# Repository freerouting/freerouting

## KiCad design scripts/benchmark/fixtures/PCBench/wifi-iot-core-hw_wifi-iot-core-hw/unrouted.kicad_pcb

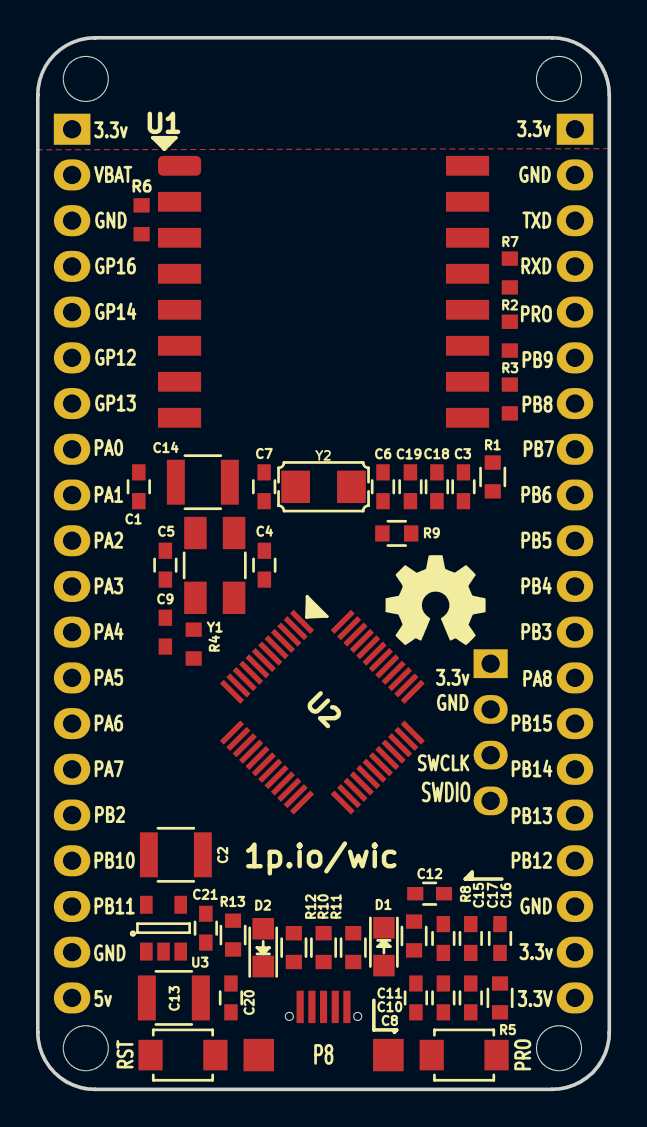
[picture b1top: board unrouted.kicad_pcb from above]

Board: 2 copper layers, 31.8 x 58.4 mm, 52 parts (0 on the bottom side), 54 nets, no tracks yet.

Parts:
C1, C9, C10, C11, C12, C15, C17, C19, C20: 0.1uF; C_0603
C2, C13, C14: 10uF-50v; C_1210
C3: 100nF; C_0603
C4, C5: 10pF; C_0603
C6: 15pF; C_0603
C7: 15pf; C_0603
C8: 470pF; C_0603
C16, C18: 1uF; C_0603
C21: 10nF; C_0603
D1: Led GPIO16; LED_0805
D2: Led; LED_0805
P1, P2: CONN_01X20; Pin_Header_Straight_1x20
P3, P4, P5, P6: CONN_01X01; MountingHole_2.5mm
P7: CONN_01X04; Pin_Header_Straight_1x04
P8: USB; Micro_usb_B_smd
PRO: SW_PUSH_SMALL_H; SW_SPST_B3U-1000P-B
R1, R6, R7, R8, R13: 10k; R_0603
R2, R3, R4, R5: 10K; R_0603
R9: 0R; R_0603
R10: 1.5K; R_0603
R11, R12: 22; R_0603
RST: RST; SW_SPST_B3U-1000P-B
U1: ESP-07v2; ESP-07v2-smd-16pin
U2: STM32F103C8Tx; LQFP-48_Pin1.7x0.3mm_Pitch0.5mm
U3: LP2985LV; SOT-23-5
VAL**: oshw_logo_500; logo5
Y1: 8MHz; Crystal_SMD_5032_4Pads
Y2: 32.687; crystal_smd_32.768_2Pin

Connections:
+3V3: C1.1, C2.1, C10.2, C11.2, C12.1, C14.1, C15.2, C16.2, C17.2, P1.1, P2.1, P2.19, P2.20, P7.1, R2.1, R4.2, R5.2, R6.1, R7.1, R8.1, R9.2, R13.1, U1.8, U2.9, U2.24, U2.36, U2.48, U3.5
+5V: C13.1, C20.1, P1.20, P8.1, U3.1, U3.3
/CH_PD: R6.2, U1.3, U2.19
/ESP_PRO: C8.1, P2.5, PRO.1, R5.1, R7.2, U1.12, U2.38
/ESP_RST: U1.1, U2.18
/ESP_RXD: P2.4, U1.15, U2.30
/ESP_TXD: P2.3, U1.16, U2.31
/GPIO16: D1.1, P1.4, U1.4
/RST: C9.1, R4.1, RST.1, U2.7
/SWCLK: P7.3, U2.37
/SWDIO: P7.4, U2.34
/USB_DIS: R10.1, U2.2
/USB_DM: R12.1, U2.32
/USB_DP: R11.1, U2.33
/VBAT: C3.2, C18.2, C19.2, P1.2, R9.1, U2.1
GNDREF: C1.2, C2.2, C3.1, C4.2, C5.2, C6.2, C7.2, C8.2, C9.2, C10.1, C11.1, C12.2, C13.2, C14.2, C15.1, C16.1, C17.1, C18.1, C19.1, C20.2, C21.2, D2.1, P1.3, P1.19, P2.2, P2.18, P8.4, P8.5, PRO.2, R1.2, R3.2, RST.2, U1.9, U3.2
GPIO12: P1.6, U1.6
GPIO13: P1.7, U1.7
GPIO14: P1.5, U1.5
unnamed: C4.1, U2.5, Y1.1
unnamed: C5.1, U2.6, Y1.2
unnamed: C6.1, U2.3, Y2.1
unnamed: C7.1, U2.4, Y2.2
unnamed: C21.1, U3.4
unnamed: D1.2, R8.2
unnamed: D2.2, R13.2
unnamed: P8.2, R12.2
unnamed: P8.3, R10.2, R11.2
unnamed: R1.1, U2.44
unnamed: R2.2, U1.11
unnamed: R3.1, U1.10
PA0: P1.8, U2.10
PA1: P1.9, U2.11
PA2: P1.10, U2.12
PA3: P1.11, U2.13
PA4: P1.12, U2.14
PA5: P1.13, U2.15
PA6: P1.14, U2.16
PA7: P1.15, U2.17
PA8: P2.13, U2.29
PB2: P1.16, U2.20
PB3: P2.12, U2.39
PB4: P2.11, U2.40
PB5: P2.10, U2.41
PB6: P2.9, U2.42
PB7: P2.8, U2.43
PB8: P2.7, U2.45
PB9: P2.6, U2.46
PB10: P1.17, U2.21
PB11: P1.18, U2.22
PB12: P2.17, U2.25
PB13: P2.16, U2.26
PB14: P2.15, U2.27
PB15: P2.14, U2.28

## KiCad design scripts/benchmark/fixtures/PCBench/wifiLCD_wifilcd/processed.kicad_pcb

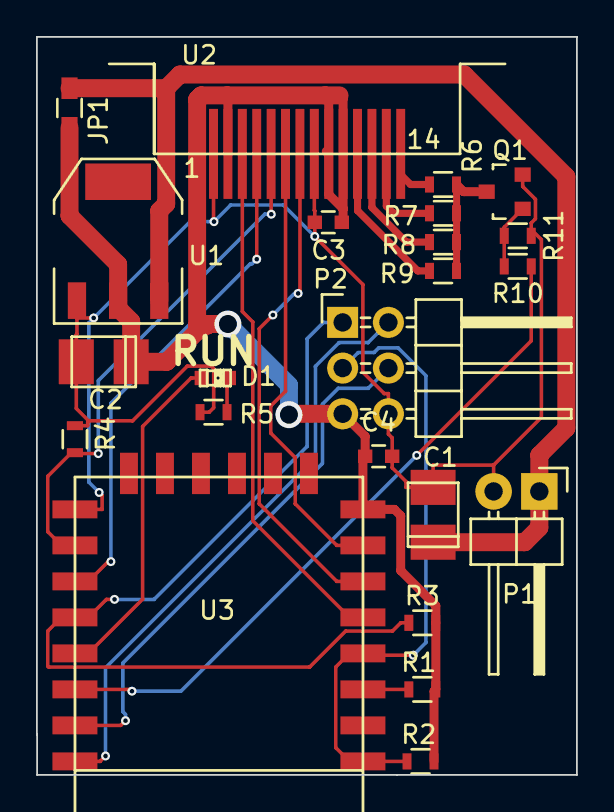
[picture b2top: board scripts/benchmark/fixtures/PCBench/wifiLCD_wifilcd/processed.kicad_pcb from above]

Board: 2 copper layers, 30.0 x 41.0 mm, 23 parts (0 on the bottom side), 22 nets.

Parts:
C1: 22uF 25V; TantalC_SizeT_EIA-3528
C2: 100uF 6.3v; TantalC_SizeT_EIA-3528
C3, C4: 100n; C_0603
D1: LED; LED-0603
JP1: JUMPER; R_0603_HandSoldering
P1: CONN_01X02; Pin_Header_Angled_1x02
P2: CONN_01X06; Pin_Header_Angled_2x03
Q1: BSS138; SOT-23
R1, R2, R3, R4: 10K; R_0603
R5: 220; R_0603
R6, R7, R8, R9: 4R7; R_0603
R10: 100k; R_0603
R11: 10; R_0603
U1: AP1117D33; SOT-223
U2: TM022HDH26; TM022HDH26_PADSONLY
U3: ESP-12E

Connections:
+3V3: C2.1, C3.1, C4.1, JP1.2, P2.5, R1.1, R2.1, R3.1, U1.2, U2.2, U2.9, U2.10, U3.8
+5V: C1.1, JP1.1, P1.1, U1.3
/BL: R11.2, U3.20
/CS: R4.1, U2.5, U3.16
/DC: U2.4, U3.17
/DTR: P2.1, R3.2, U3.18
/MISO: U2.7, U3.6
/MOSI: U2.6, U3.7
/RTS: P2.3, R2.2, U3.1, U3.4
/RX: P2.2, U3.22
/SCL: U2.3, U3.5
/TX: P2.4, U3.21
GND: C1.2, C2.2, C3.2, C4.2, P1.2, P2.6, Q1.2, R4.2, R5.2, R10.1, U1.1, U2.1, U2.8, U3.15
unnamed: D1.1, R5.1
unnamed: D1.2, U3.19
unnamed: Q1.1, R10.2, R11.1
unnamed: Q1.3, R6.1, R7.1, R8.1, R9.1
unnamed: R1.2, U3.3
unnamed: R6.2, U2.14
unnamed: R7.2, U2.13
unnamed: R8.2, U2.12
unnamed: R9.2, U2.11

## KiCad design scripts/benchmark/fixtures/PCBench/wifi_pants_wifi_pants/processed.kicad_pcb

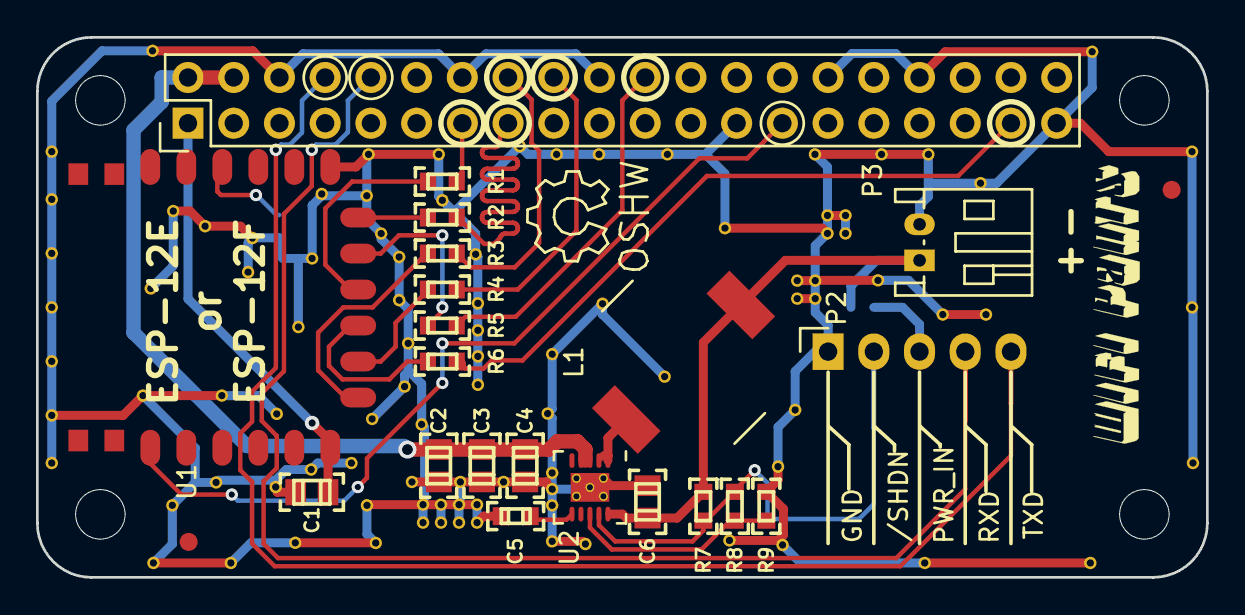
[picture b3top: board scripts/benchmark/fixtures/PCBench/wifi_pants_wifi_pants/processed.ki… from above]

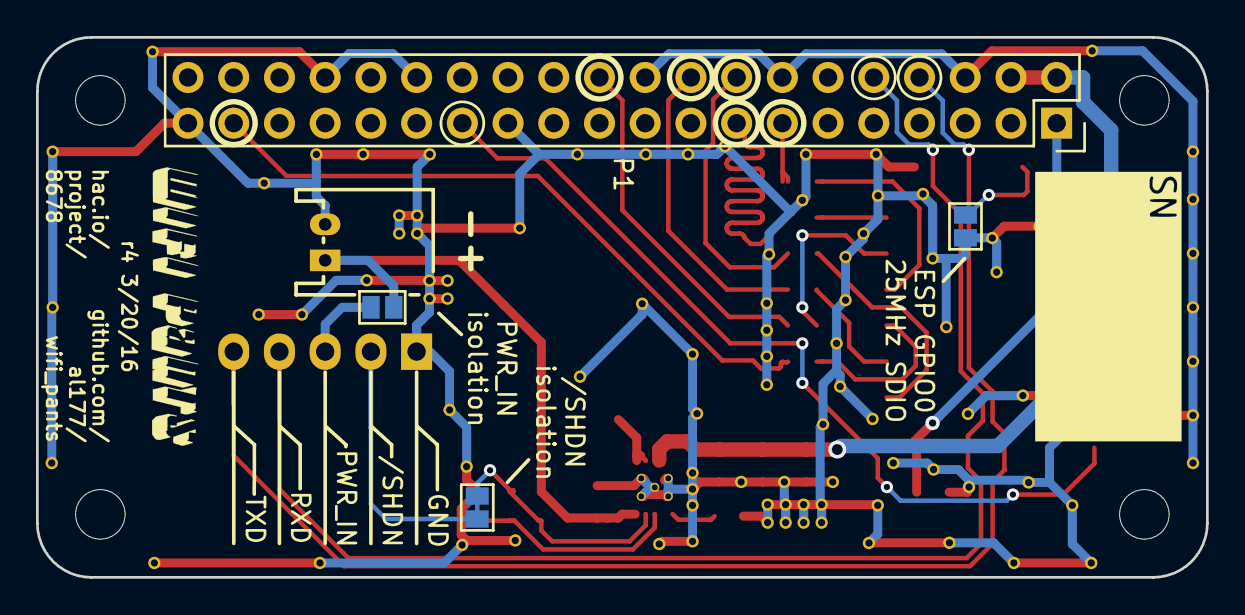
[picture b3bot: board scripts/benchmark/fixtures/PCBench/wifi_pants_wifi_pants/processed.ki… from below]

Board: 2 copper layers, 65.0 x 30.0 mm, 28 parts (4 on the bottom side), 25 nets.

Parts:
C1, C2, C3, C4: 10uF X5R; 0805(2012m)-CHIP-CAP
C5: 0.15uF X5R; 0603(1608m)-CHIP-CAP
C6: 22uF X5R; 0805(2012m)-CHIP-CAP
JP1: /PSU_SHDN ISOL; GS2
JP2: PWR_IN ISOL; GS2
JP3: GPIO0; GS2
L1: 1.0uH; SRU1028-1R
P1: CONN_02X20; Socket_Strip_Straight_2x20_pi
P2: POWER / UART; Pin_Header_Angled_1x05_mirror
P3: JST PH POWER IN; Connectors_JST_S2B-PH-K
R1, R2, R3, R4, R5, R6: 33; 0603(1608m)-CHIP-RESISTOR
R7: 47K 1%; 0603(1608m)-CHIP-RESISTOR
R8: 33K 1%; 0603(1608m)-CHIP-RESISTOR
R9: 1K 1%; 0603(1608m)-CHIP-RESISTOR
U1: ESP-12E; ESP-12E-narrow
U2: TPS6123x; VSON-10
W1, W1_2, W1_3, W1_4: MOUNT; NPTH_Hole_2_75mm

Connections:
+3V3: C1.1, P1.1, U1.8
+5V: C2.1, C3.1, C4.1, P1.2, P1.4, U2.3, U2.4
//CS: R3.2, U1.9
//HOLD: R6.2, U1.11
//WP: R1.2, U1.12
/CLK: R2.2, U1.14
/SHDN: JP1.1, JP1.2, P2.2, R7.2, R8.1, U2.9
/SI: R5.2, U1.13
/SO: R4.2, U1.10
GND: C1.2, C2.2, C3.2, C4.2, C5.2, C6.2, JP3.2, P1.6, P1.14, P1.20, P1.25, P1.30, P1.34, P1.39, P2.1, P3.2, R9.2, U1.15, U2.11
ID_SD: P1.27, U1.3
unnamed: C5.1, U2.6
unnamed: JP2.2, P2.3
unnamed: JP3.1, U1.18
unnamed: L1.2, U2.1, U2.2
unnamed: R8.2, R9.1, U2.8
PI_UART0_RXD: P1.10, P2.4
PI_UART0_TXD: P1.8, P2.5
PWR_IN: C6.1, JP2.1, L1.1, P3.1, R7.1, U2.10
SD_CLK: P1.15, R2.1
SD_CMD: P1.16, R3.1
SD_D0: P1.18, R4.1
SD_D1: P1.22, R5.1
SD_D2: P1.37, R6.1
SD_D3: P1.13, R1.1

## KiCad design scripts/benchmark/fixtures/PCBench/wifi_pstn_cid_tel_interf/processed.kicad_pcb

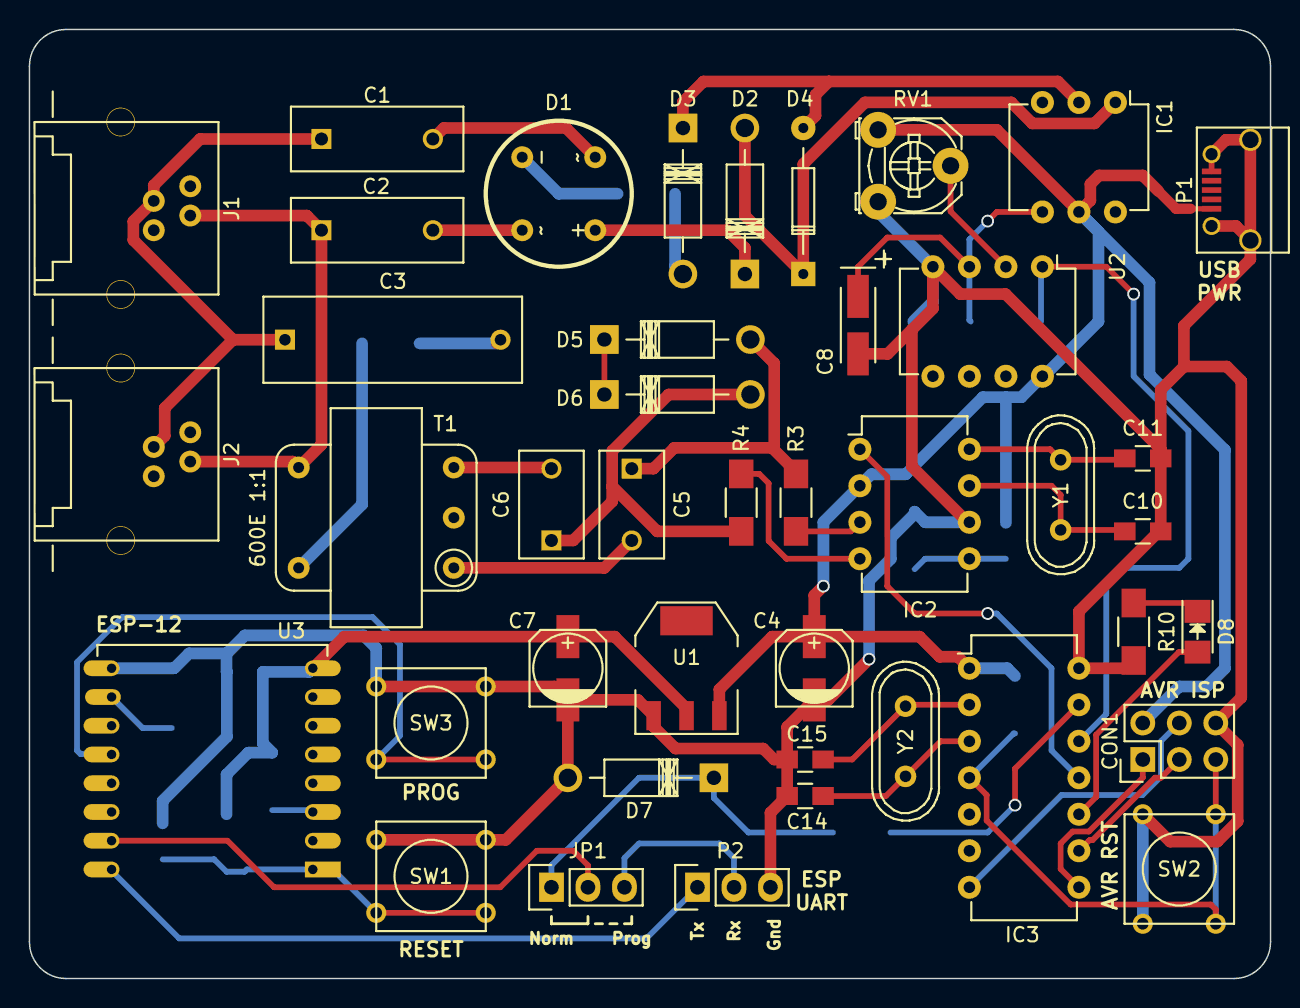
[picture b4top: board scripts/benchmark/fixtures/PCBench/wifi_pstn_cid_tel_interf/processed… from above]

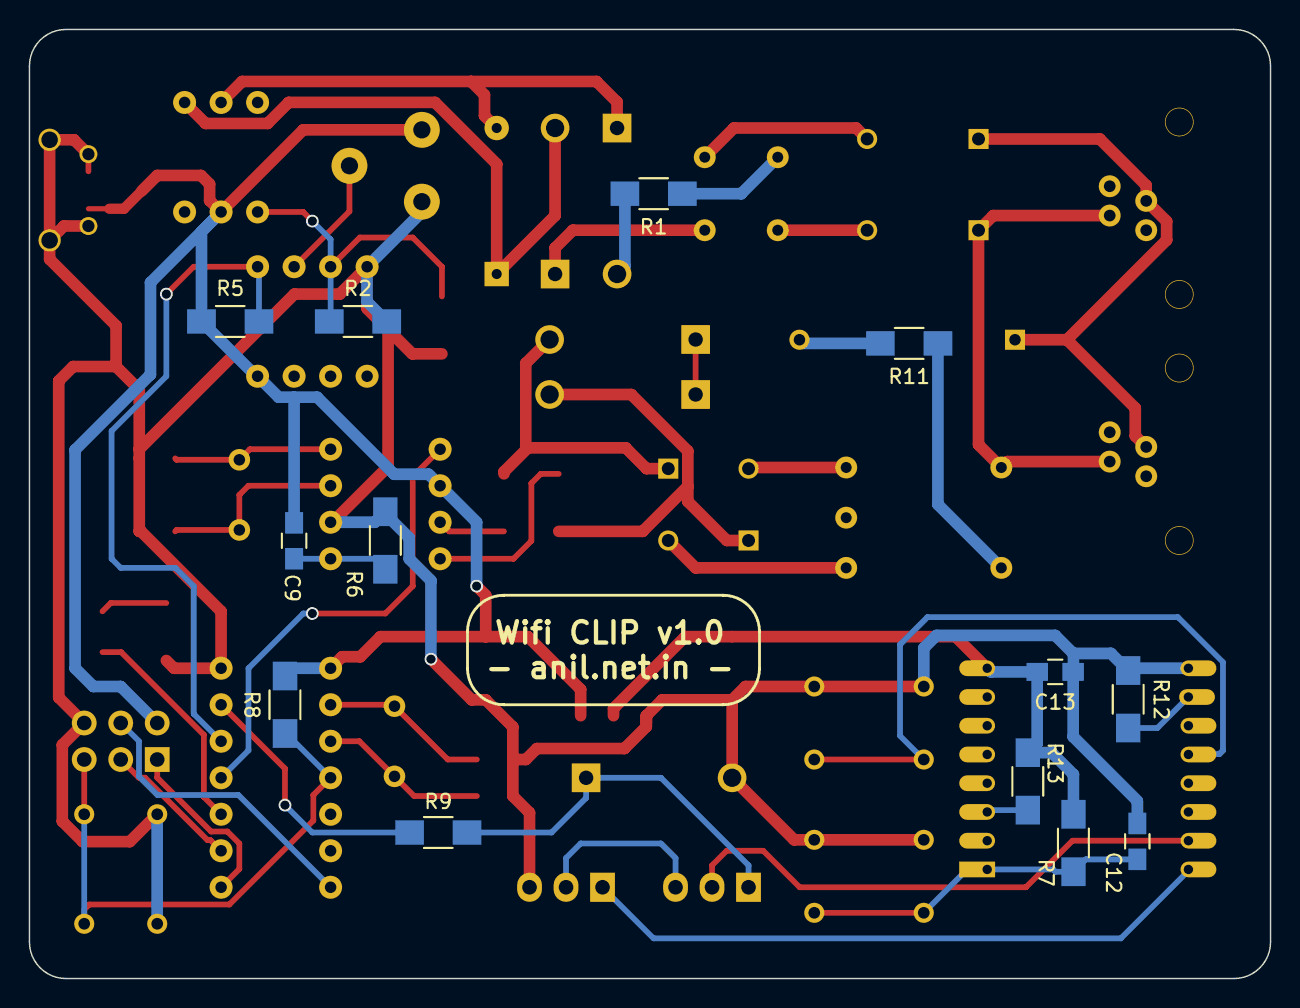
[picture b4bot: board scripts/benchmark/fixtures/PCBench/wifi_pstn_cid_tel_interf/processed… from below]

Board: 2 copper layers, 86.4 x 66.0 mm, 55 parts (13 on the bottom side), 45 nets.

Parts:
C1: 33nF, 150V; C_Disc_D12_P7.75
C2: 33nF, 150v; C_Disc_D12_P7.75
C3: 100nF, 250V; C_Rect_L18_W6_P15
C4, C7: 10uF; c_elec_5x5.3
C5, C6: 47nF; C_Disc_D7.5_P5
C8: 1uF; TantalC_SizeA_EIA-3216_HandSoldering
C9, C12, C13: 0.1uF; C_0805_HandSoldering
C10, C11, C14, C15: 22pF; C_0805_HandSoldering
CON1: AVR-ISP-6; Pin_Header_Straight_2x03
D1: W10M; WOM_BRIDGE
D2, D3: ZENER 8.2V; Diode_DO-41_SOD81_Horizontal_RM10
D4: 1N4148; Diode_DO-35_SOD27_Horizontal_RM10
D5, D6: ZENER 3.3V; Diode_DO-41_SOD81_Horizontal_RM10
D7: 3.3v; Diode_DO-41_SOD81_Horizontal_RM10
D8: LED; LED-1206
IC1: 4N35; DIP-6_W7.62mm
IC2: HT9032D; DIP-8_W7.62mm
IC3: ATTINY84-P; DIP-14_W7.62mm
J1, J2: RJ11_PTH_STAGGER; RJ11_PTH_6P4C_STAG
JP1: RX sel.; Pin_Header_Straight_1x03
P1: USB_OTG; USB_Micro-B
P2: ESP_UART; Pin_Header_Straight_1x03
R1, R6: 100K; R_1206_HandSoldering
R2, R3, R4: 220K; R_1206_HandSoldering
R5: 10K; R_1206_HandSoldering
R7, R8: 4.7K; R_1206_HandSoldering
R9: 1k; R_1206_HandSoldering
R10, R11, R12, R13: 1K; R_1206_HandSoldering
RV1: 10K; Potentiometer_Triwood_RM-065
SW1: ESP_REST; SW_PUSH_SMALL
SW2: AVR_REST; SW_PUSH_SMALL
SW3: PROG; SW_PUSH_SMALL
T1: 600E 1:1; TRANSFO-AUDIO-EL14
U1: LD1117S33TR; SOT-223
U2: LM393; DIP-8_W7.62mm
U3: ESP-12
Y1: 3.579545Mhz; Crystal_HC49-U_Vertical
Y2: 8 Mhz; Crystal_HC49-U_Vertical

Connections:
+3V3: C7.1, C13.2, R7.1, R13.1, U1.2, U3.8
+5V: C4.1, C9.1, CON1.2, IC1.5, IC2.2, IC3.1, P1.1, R5.1, R8.2, RV1.1, U1.3, U2.8
AVR_MISO: CON1.1, IC3.8
AVR_MOSI: CON1.4, IC3.7
AVR_REST: CON1.5, IC3.4, R8.1, SW2.2
AVR_SCL: CON1.3, IC3.9
CLIP: IC2.1, IC3.11
GND: C4.2, C7.2, C8.2, C10.2, C11.2, C12.2, C13.1, C14.2, C15.2, CON1.6, D7.2, IC2.6, IC3.14, P1.5, P1.6, P2.3, R2.2, R6.2, R10.2, R12.1, RV1.3, SW1.1, SW2.1, SW3.1, U1.1, U2.4, U3.9
NUMOUT: IC3.13, R9.1
unnamed: C1.2, D1.4
unnamed: C2.2, D1.2
unnamed: C3.2, R11.2
unnamed: C5.1, D5.2, R3.1
unnamed: C5.2, T1.1
unnamed: C6.1, D6.2, R4.1
unnamed: C6.2, T1.3
unnamed: C8.1, IC1.4, R2.1, U2.3
unnamed: C9.2, IC2.5, R6.1
unnamed: C10.1, IC2.7, Y1.1
unnamed: C11.1, IC2.8, Y1.2
unnamed: C12.1, R7.2, SW1.2, U3.1
unnamed: C14.1, IC3.3, Y2.1
unnamed: C15.1, IC3.2, Y2.2
unnamed: D1.1, D2.1
unnamed: D1.3, R1.1
unnamed: D2.2, D4.1, IC1.1
unnamed: D3.1, D4.2, IC1.2
unnamed: D3.2, R1.2
unnamed: D5.1, D6.1
unnamed: D7.1, JP1.1, R9.2
unnamed: D8.1, R10.1
unnamed: D8.2, IC3.10
unnamed: IC2.3, R3.2
unnamed: IC2.4, R4.2
unnamed: JP1.2, U3.15
unnamed: JP1.3, P2.2
unnamed: P2.1, U3.16
unnamed: R11.1, T1.5
unnamed: R12.2, U3.10
unnamed: R13.2, U3.3
unnamed: RV1.2, U2.2
unnamed: SW3.2, U3.12
RING: IC3.12, R5.2, U2.1
TEL1: C1.1, C3.1, J1.2, J2.2
TEL2: C2.1, J1.3, J2.3, T1.4

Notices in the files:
scripts/benchmark/fixtures/PCBench/wifi_pants_wifi_pants/processed.kicad_pcb:
Licensed under Creative Commons Attribution Share-Alike
